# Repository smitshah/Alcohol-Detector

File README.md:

# Alcohol-Detector

**INTRODUCTION**

For effective detection of Alcohol Concentration, we are using MQ3 Gas Sensor, which is cheap and portable. Our product will sense the amount of alcohol consumed by the person and it will display the same to the LCD. This product can be used for identifying whether the person is drunk, which is used by traffic police across many countries .If the person inside car has consumed alcohol then it is detected by the sensor. The sensed value is displayed on the 16x2 LCD Display. 

The MQ3 Alcohol sensor detects the alcohol consumption by the smell of the breath. The sensor is an analog as well as a digital sensor which on its analog pin outputs the analog voltage proportional to the alcohol level. 
For different countries, the level of alcohol in the blood that defines a person as over the limit for driving varies. The range ranges from 0.01 to 0.10. 

Most countries have a limit of about 0.05. 

For example, Greece, Greenland, and Iceland all have limits of 0.05. Canada has a higher limit set at 0.08. 

In the United States, it is also 0.08. 

In India, the permissible blood alcohol content (BAC) is set at 0.03% per 100ml blood.

**COMPONENTS USED**

* Arduino Uno
* MQ-3 Alcohol Sensor
* 16X2 LCD
* GPP (General Purpose PCB)
* 10k Pot
* Jumper Wires
* Resistors

**Circuit Diagram**

**Application of the project**

* Used in cars for engine locking.
* Used as a alcohol detector machine.

**Conclusion**

We have made an Alcohol Detector, which will detect alcohol and give alert when alcohol level in mixture of carbon dioxide and methanol is more 400. By using this, product in cars i.e. by installing this near steering and using this as engine locking system we can reduce the rate of accidents that take place due to drink and drive.

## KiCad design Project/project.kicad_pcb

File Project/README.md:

I have attached the KiCAD Schematic of my project. In my actual project I have done it with Arduino, but initially I have started the project with 8051, but I was not able to complete that due to lack of Development Board of 8051.

I have also added 8051 file if any one want to do it using 8051. The name of the file is proj.asm

The Gerber files of PCB are in pdf format, but you can also save it in .gbr format by opening the project.

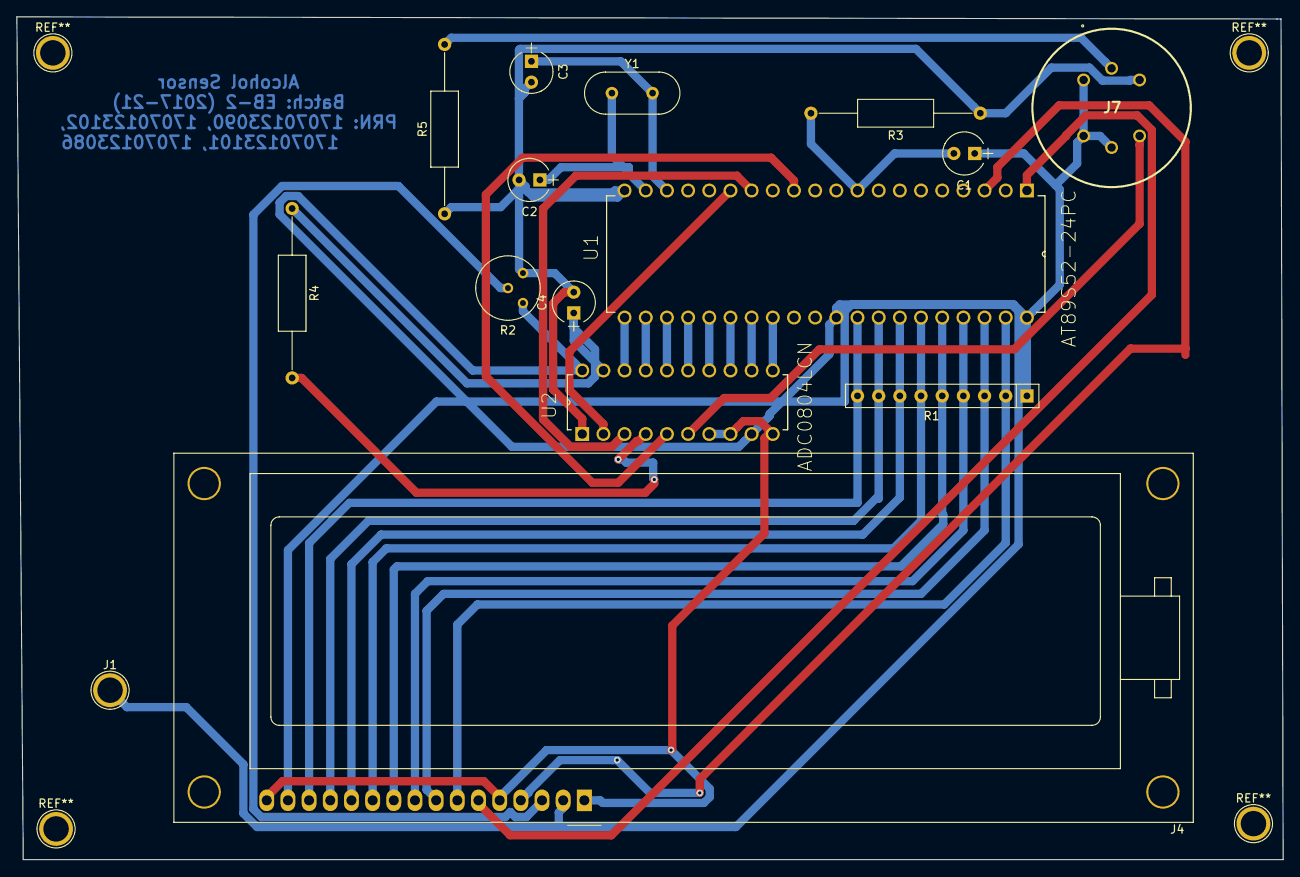
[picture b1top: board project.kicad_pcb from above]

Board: 2 copper layers, 151.9 x 101.1 mm, 15 parts (0 on the bottom side), 31 nets.

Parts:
C1: 10uf; CP_Radial_Tantal_D5.0mm_P2.50mm
C2, C3: 22pf; CP_Radial_Tantal_D5.0mm_P2.50mm
C4: 150pf; CP_Radial_Tantal_D5.0mm_P2.50mm
J1: VCC; 1pin
J4: LCD 16x2; HY1602E
J7: MQ 3; MQ-3
R1: Resistor SIP 9; R_Array_SIP9
R2: 10k; Potentiometer_Trimmer_Bourns_3339H_Horizontal
R3: 8.2k; R_Axial_DIN0309_L9.0mm_D3.2mm_P20.32mm_Horizontal
R4, R5: 10k; R_Axial_DIN0309_L9.0mm_D3.2mm_P20.32mm_Horizontal
U1: AT89S52-24PC; DIP254P1524X482-40
U2: ADC0804LCN; DIP254P762X508-20
Y1: Crystal; Crystal_HC49-4H_Vertical

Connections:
GND: C2.2, C3.2, C4.2, J4.1, J4.5, J4.16, J7.5, R2.1, R3.1, R5.1, U1.20, U2.1, U2.7, U2.8, U2.10
unnamed: C1.1, J1.1, J4.2, J4.15, J7.1, J7.2, J7.3, R1.1, R2.3, U1.31, U1.40, U2.9, U2.20
unnamed: C1.2, R3.2, U1.9
unnamed: C2.1, U1.19, Y1.1
unnamed: C3.1, U1.18, Y1.2
unnamed: C4.1, R4.1, U2.19
unnamed: J4.3, R2.2
unnamed: J4.4, U1.3
unnamed: J4.6, U1.1
unnamed: J4.7, R1.2, U1.39
unnamed: J4.8, R1.3, U1.38
unnamed: J4.9, R1.4, U1.37
unnamed: J4.10, R1.5, U1.36
unnamed: J4.11, R1.6, U1.35
unnamed: J4.12, R1.7, U1.34
unnamed: J4.13, R1.8, U1.33
unnamed: J4.14, R1.9, U1.32
unnamed: J7.4, U2.6
unnamed: J7.6, R5.2
unnamed: R4.2, U2.4
unnamed: U1.12, U2.5
unnamed: U1.14, U2.3
unnamed: U1.15, U2.2
unnamed: U1.21, U2.18
unnamed: U1.22, U2.17
unnamed: U1.23, U2.16
unnamed: U1.24, U2.15
unnamed: U1.25, U2.14
unnamed: U1.26, U2.13
unnamed: U1.27, U2.12
unnamed: U1.28, U2.11
